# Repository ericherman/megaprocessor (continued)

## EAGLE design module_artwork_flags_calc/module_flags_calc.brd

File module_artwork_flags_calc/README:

Flag Calculation

The status flags are calculated using the results generated by various
parts of the processor, in particular the ALU, depending on the
instruction being executed. They are stored in the status register.

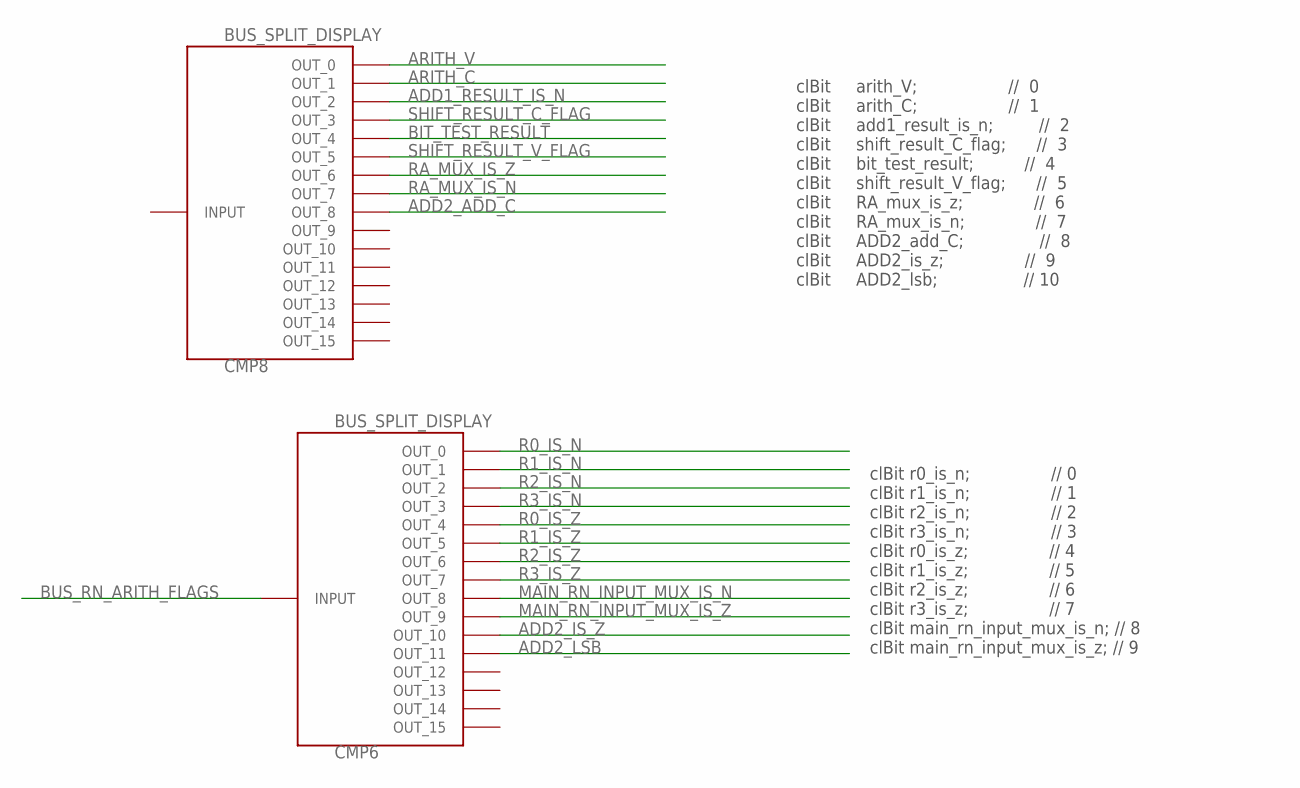
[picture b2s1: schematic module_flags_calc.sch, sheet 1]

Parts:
CMP6, CMP8: BUS_SPLIT_DISPLAY

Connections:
ADD1_RESULT_IS_N: CMP8.P$3 (OUT_2); also elsewhere on the board
ADD2_ADD_C: CMP8.P$9 (OUT_8); also elsewhere on the board
ADD2_IS_Z: CMP6.P$11 (OUT_10); also elsewhere on the board
ADD2_LSB: CMP6.P$12 (OUT_11); also elsewhere on the board
ARITH_C: CMP8.P$2 (OUT_1); also elsewhere on the board
ARITH_V: CMP8.P$1 (OUT_0); also elsewhere on the board
BIT_TEST_RESULT: CMP8.P$5 (OUT_4); also elsewhere on the board
BUS_RN_ARITH_FLAGS: CMP6.INPUT
MAIN_RN_INPUT_MUX_IS_N: CMP6.P$9 (OUT_8); also elsewhere on the board
MAIN_RN_INPUT_MUX_IS_Z: CMP6.P$10 (OUT_9); also elsewhere on the board
R0_IS_N: CMP6.P$1 (OUT_0); also elsewhere on the board
R0_IS_Z: CMP6.P$5 (OUT_4)
R1_IS_N: CMP6.P$2 (OUT_1); also elsewhere on the board
R1_IS_Z: CMP6.P$6 (OUT_5)
R2_IS_N: CMP6.P$3 (OUT_2)
R2_IS_Z: CMP6.P$7 (OUT_6)
R3_IS_N: CMP6.P$4 (OUT_3)
R3_IS_Z: CMP6.P$8 (OUT_7)
RA_MUX_IS_N: CMP8.P$8 (OUT_7); also elsewhere on the board
RA_MUX_IS_Z: CMP8.P$7 (OUT_6); also elsewhere on the board
SHIFT_RESULT_C_FLAG: CMP8.P$4 (OUT_3); also elsewhere on the board
SHIFT_RESULT_V_FLAG: CMP8.P$6 (OUT_5); also elsewhere on the board

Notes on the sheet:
clBit arith_V; // 0 clBit arith_C; // 1 clBit add1_result_is_n; // 2 clBit shift_result_C_flag; // 3 clBit bit_test_result; // 4 clBit shift_result_V_flag; // 5 clBit RA_mux_is_z; // 6 clBit RA_mux_is_n; // 7 clBit ADD2_add_C; // 8 clBit ADD2_is_z; // 9 clBit ADD2_lsb; // 10
clBit r0_is_n; // 0 clBit r1_is_n; // 1 clBit r2_is_n; // 2 clBit r3_is_n; // 3 clBit r0_is_z; // 4 clBit r1_is_z; // 5 clBit r2_is_z; // 6 clBit r3_is_z; // 7 clBit main_rn_input_mux_is_n; // 8 clBit main_rn_input_mux_is_z; // 9

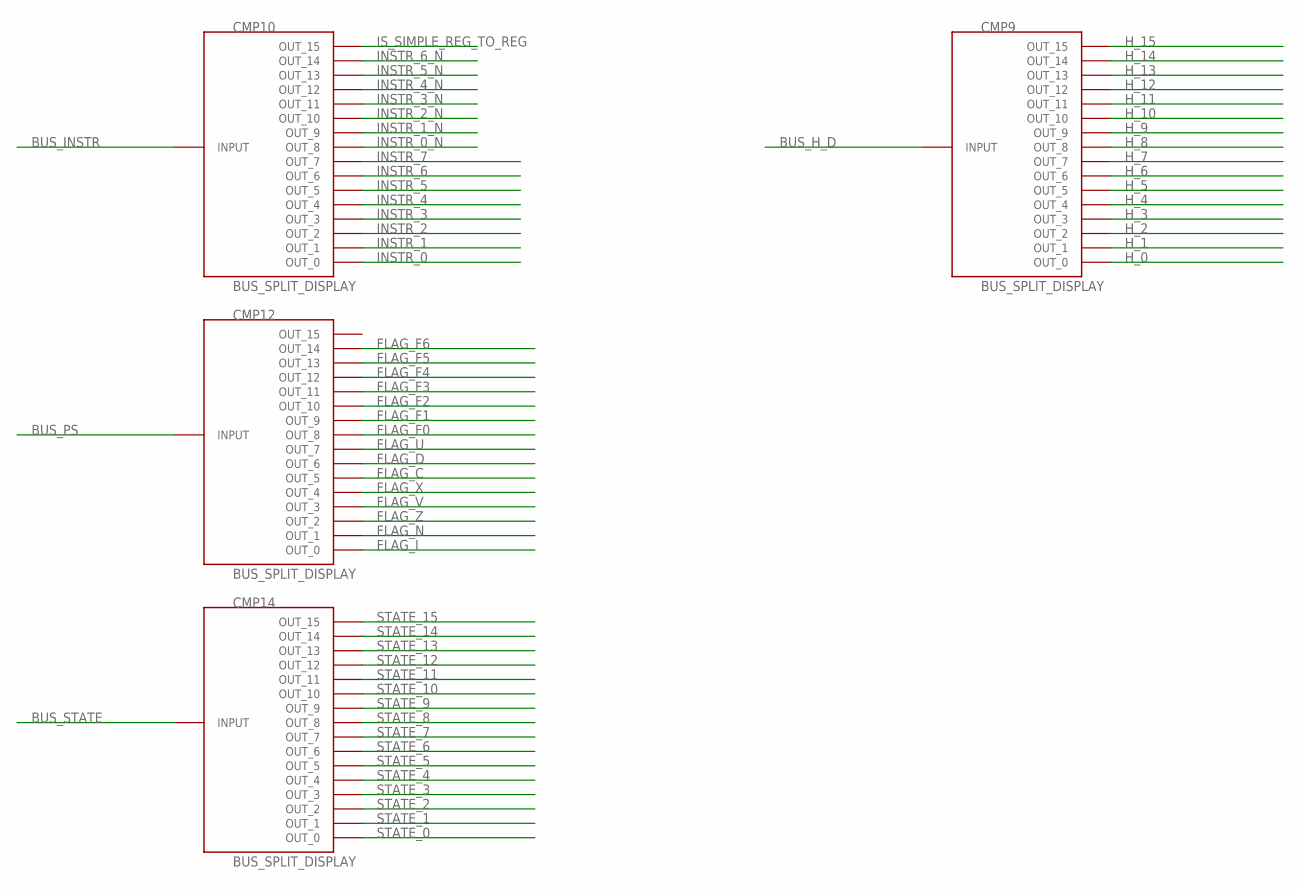
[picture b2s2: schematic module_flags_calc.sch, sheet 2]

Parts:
CMP9, CMP10, CMP12, CMP14: BUS_SPLIT_DISPLAY

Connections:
BUS_H_D: CMP9.INPUT
BUS_INSTR: CMP10.INPUT
BUS_PS: CMP12.INPUT
BUS_STATE: CMP14.INPUT
FLAG_C: CMP12.P$6 (OUT_5); also elsewhere on the board
FLAG_D: CMP12.P$7 (OUT_6); also elsewhere on the board
FLAG_F0: CMP12.P$9 (OUT_8); also elsewhere on the board
FLAG_F1: CMP12.P$10 (OUT_9); also elsewhere on the board
FLAG_F2: CMP12.P$11 (OUT_10)
FLAG_F3: CMP12.P$12 (OUT_11)
FLAG_F4: CMP12.P$13 (OUT_12); also elsewhere on the board
FLAG_F5: CMP12.P$14 (OUT_13); also elsewhere on the board
FLAG_F6: CMP12.P$15 (OUT_14); also elsewhere on the board
FLAG_I: CMP12.P$1 (OUT_0); also elsewhere on the board
FLAG_N: CMP12.P$2 (OUT_1); also elsewhere on the board
FLAG_U: CMP12.P$8 (OUT_7); also elsewhere on the board
FLAG_V: CMP12.P$4 (OUT_3); also elsewhere on the board
FLAG_X: CMP12.P$5 (OUT_4); also elsewhere on the board
FLAG_Z: CMP12.P$3 (OUT_2); also elsewhere on the board
H_0: CMP9.P$1 (OUT_0)
H_1: CMP9.P$2 (OUT_1)
H_2: CMP9.P$3 (OUT_2)
H_3: CMP9.P$4 (OUT_3); also elsewhere on the board
H_4: CMP9.P$5 (OUT_4); also elsewhere on the board
H_5: CMP9.P$6 (OUT_5); also elsewhere on the board
H_6: CMP9.P$7 (OUT_6)
H_7: CMP9.P$8 (OUT_7)
H_8: CMP9.P$9 (OUT_8)
H_9: CMP9.P$10 (OUT_9)
H_10: CMP9.P$11 (OUT_10)
H_11: CMP9.P$12 (OUT_11)
H_12: CMP9.P$13 (OUT_12)
H_13: CMP9.P$14 (OUT_13)
H_14: CMP9.P$15 (OUT_14)
H_15: CMP9.P$16 (OUT_15)
INSTR_0: CMP10.P$1 (OUT_0); also elsewhere on the board
INSTR_0_N: CMP10.P$9 (OUT_8)
INSTR_1: CMP10.P$2 (OUT_1); also elsewhere on the board
INSTR_1_N: CMP10.P$10 (OUT_9)
INSTR_2: CMP10.P$3 (OUT_2); also elsewhere on the board
INSTR_2_N: CMP10.P$11 (OUT_10)
INSTR_3: CMP10.P$4 (OUT_3); also elsewhere on the board
INSTR_3_N: CMP10.P$12 (OUT_11)
INSTR_4: CMP10.P$5 (OUT_4)
INSTR_4_N: CMP10.P$13 (OUT_12)
INSTR_5: CMP10.P$6 (OUT_5)
INSTR_5_N: CMP10.P$14 (OUT_13)
INSTR_6: CMP10.P$7 (OUT_6)
INSTR_6_N: CMP10.P$15 (OUT_14); also elsewhere on the board
INSTR_7: CMP10.P$8 (OUT_7)
IS_SIMPLE_REG_TO_REG: CMP10.P$16 (OUT_15); also elsewhere on the board
STATE_0: CMP14.P$1 (OUT_0); also elsewhere on the board
STATE_1: CMP14.P$2 (OUT_1); also elsewhere on the board
STATE_2: CMP14.P$3 (OUT_2)
STATE_3: CMP14.P$4 (OUT_3); also elsewhere on the board
STATE_4: CMP14.P$5 (OUT_4)
STATE_5: CMP14.P$6 (OUT_5); also elsewhere on the board
STATE_6: CMP14.P$7 (OUT_6)
STATE_7: CMP14.P$8 (OUT_7)
STATE_8: CMP14.P$9 (OUT_8); also elsewhere on the board
STATE_9: CMP14.P$10 (OUT_9); also elsewhere on the board
STATE_10: CMP14.P$11 (OUT_10)
STATE_11: CMP14.P$12 (OUT_11)
STATE_12: CMP14.P$13 (OUT_12)
STATE_13: CMP14.P$14 (OUT_13); also elsewhere on the board
STATE_14: CMP14.P$15 (OUT_14)
STATE_15: CMP14.P$16 (OUT_15)

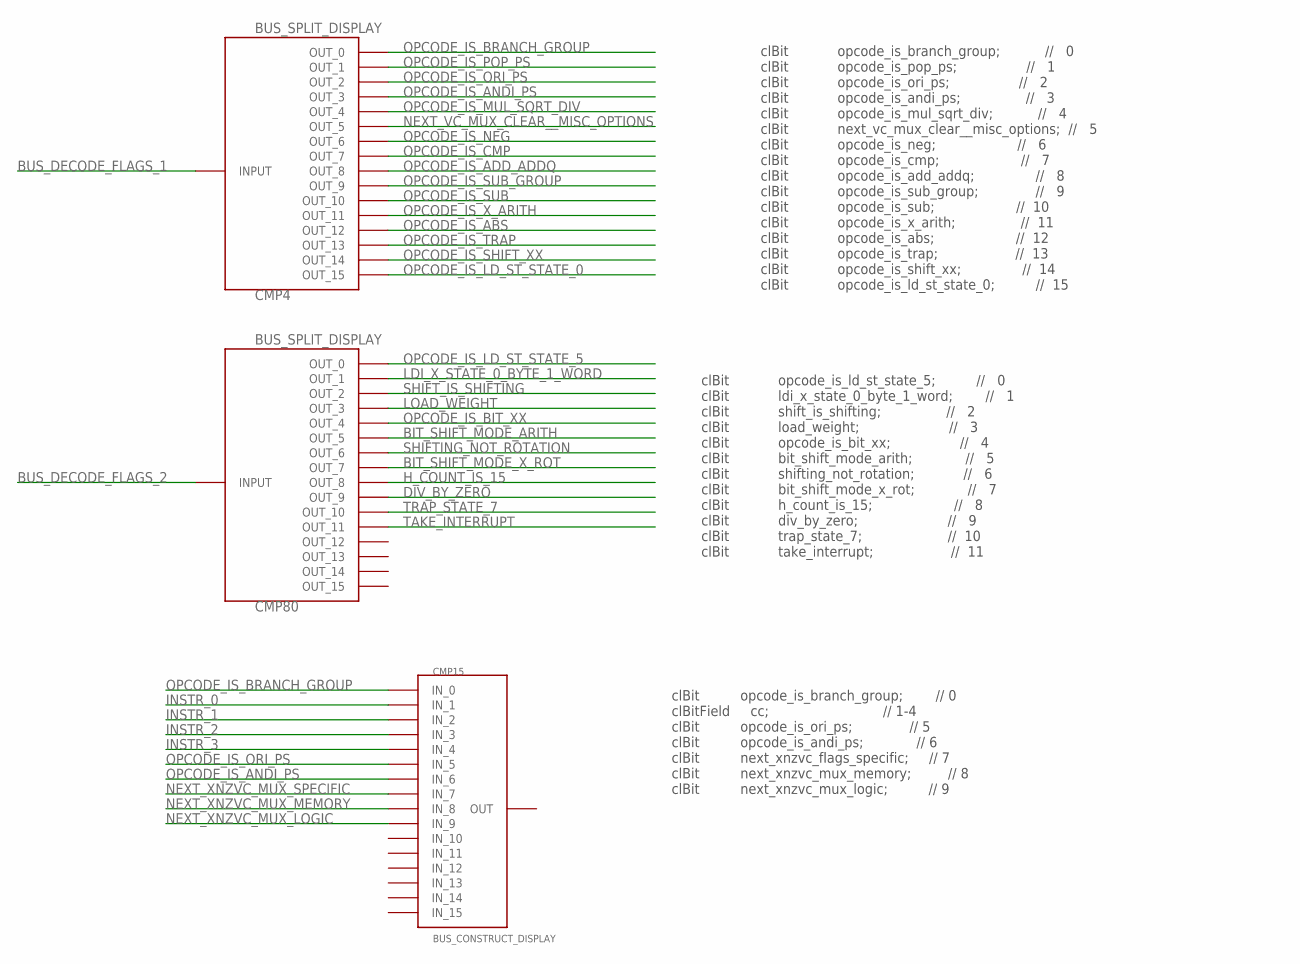
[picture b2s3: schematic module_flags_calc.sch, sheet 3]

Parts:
CMP4, CMP80: BUS_SPLIT_DISPLAY
CMP15: BUS_CONSTRUCT_DISPLAY; BUS_SPLIT_DISPLAY

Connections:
BIT_SHIFT_MODE_ARITH: CMP80.P$6 (OUT_5); also elsewhere on the board
BIT_SHIFT_MODE_X_ROT: CMP80.P$8 (OUT_7); also elsewhere on the board
BUS_DECODE_FLAGS_1: CMP4.INPUT
BUS_DECODE_FLAGS_2: CMP80.INPUT
DIV_BY_ZERO: CMP80.P$10 (OUT_9); also elsewhere on the board
H_COUNT_IS_15: CMP80.P$9 (OUT_8); also elsewhere on the board
INSTR_0: CMP15.P$2 (IN_1); also elsewhere on the board
INSTR_1: CMP15.P$3 (IN_2); also elsewhere on the board
INSTR_2: CMP15.P$4 (IN_3); also elsewhere on the board
INSTR_3: CMP15.P$5 (IN_4); also elsewhere on the board
LDI_X_STATE_0_BYTE_1_WORD: CMP80.P$2 (OUT_1); also elsewhere on the board
LOAD_WEIGHT: CMP80.P$4 (OUT_3); also elsewhere on the board
NEXT_VC_MUX_CLEAR__MISC_OPTIONS: CMP4.P$6 (OUT_5); also elsewhere on the board
NEXT_XNZVC_MUX_LOGIC: CMP15.P$10 (IN_9); also elsewhere on the board
NEXT_XNZVC_MUX_MEMORY: CMP15.P$9 (IN_8); also elsewhere on the board
NEXT_XNZVC_MUX_SPECIFIC: CMP15.P$8 (IN_7); also elsewhere on the board
OPCODE_IS_ABS: CMP4.P$13 (OUT_12); also elsewhere on the board
OPCODE_IS_ADD_ADDQ: CMP4.P$9 (OUT_8); also elsewhere on the board
OPCODE_IS_ANDI_PS: CMP4.P$4 (OUT_3), CMP15.P$7 (IN_6); also elsewhere on the board
OPCODE_IS_BIT_XX: CMP80.P$5 (OUT_4); also elsewhere on the board
OPCODE_IS_BRANCH_GROUP: CMP4.P$1 (OUT_0), CMP15.P$1 (IN_0)
OPCODE_IS_CMP: CMP4.P$8 (OUT_7); also elsewhere on the board
OPCODE_IS_LD_ST_STATE_0: CMP4.P$16 (OUT_15); also elsewhere on the board
OPCODE_IS_LD_ST_STATE_5: CMP80.P$1 (OUT_0); also elsewhere on the board
OPCODE_IS_MUL_SQRT_DIV: CMP4.P$5 (OUT_4); also elsewhere on the board
OPCODE_IS_NEG: CMP4.P$7 (OUT_6); also elsewhere on the board
OPCODE_IS_ORI_PS: CMP4.P$3 (OUT_2), CMP15.P$6 (IN_5); also elsewhere on the board
OPCODE_IS_POP_PS: CMP4.P$2 (OUT_1); also elsewhere on the board
OPCODE_IS_SHIFT_XX: CMP4.P$15 (OUT_14); also elsewhere on the board
OPCODE_IS_SUB: CMP4.P$11 (OUT_10); also elsewhere on the board
OPCODE_IS_SUB_GROUP: CMP4.P$10 (OUT_9); also elsewhere on the board
OPCODE_IS_TRAP: CMP4.P$14 (OUT_13); also elsewhere on the board
OPCODE_IS_X_ARITH: CMP4.P$12 (OUT_11); also elsewhere on the board
SHIFTING_NOT_ROTATION: CMP80.P$7 (OUT_6); also elsewhere on the board
SHIFT_IS_SHIFTING: CMP80.P$3 (OUT_2); also elsewhere on the board
TAKE_INTERRUPT: CMP80.P$12 (OUT_11); also elsewhere on the board
TRAP_STATE_7: CMP80.P$11 (OUT_10); also elsewhere on the board

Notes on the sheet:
clBit opcode_is_branch_group; // 0 clBit opcode_is_pop_ps; // 1 clBit opcode_is_ori_ps; // 2 clBit opcode_is_andi_ps; // 3 clBit opcode_is_mul_sqrt_div; // 4 clBit next_vc_mux_clear__misc_options; // 5 clBit opcode_is_neg; // 6 clBit opcode_is_cmp; // 7 clBit opcode_is_add_addq; // 8 clBit opcode_i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
clBit opcode_is_ld_st_state_5; // 0 clBit ldi_x_state_0_byte_1_word; // 1 clBit shift_is_shifting; // 2 clBit load_weight; // 3 clBit opcode_is_bit_xx; // 4 clBit bit_shift_mode_arith; // 5 clBit shifting_not_rotation; // 6 clBit bit_shift_mode_x_rot; // 7 clBit h_count_is_15; // 8 clBit div_by_zer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
clBit opcode_is_branch_group; // 0 clBitField cc; // 1-4 clBit opcode_is_ori_ps; // 5 clBit opcode_is_andi_ps; // 6 clBit next_xnzvc_flags_specific; // 7 clBit next_xnzvc_mux_memory; // 8 clBit next_xnzvc_mux_logic; // 9

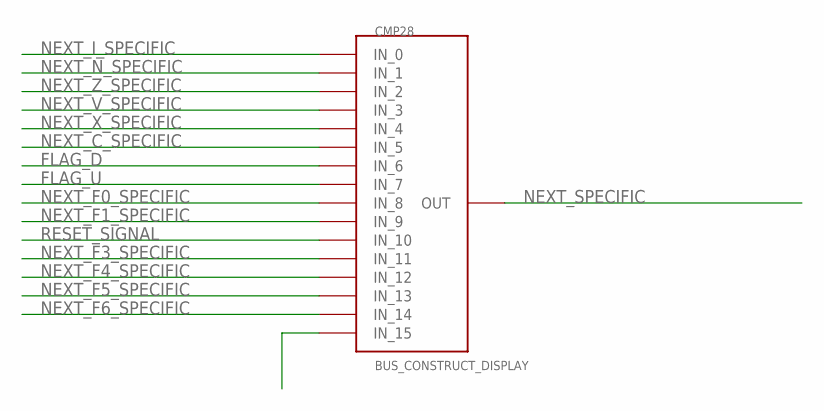
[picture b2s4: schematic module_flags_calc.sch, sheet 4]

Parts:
CMP28: BUS_CONSTRUCT_DISPLAY; BUS_SPLIT_DISPLAY

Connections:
FLAG_D: CMP28.P$7 (IN_6); also elsewhere on the board
FLAG_U: CMP28.P$8 (IN_7); also elsewhere on the board
NEXT_C_SPECIFIC: CMP28.P$6 (IN_5); also elsewhere on the board
NEXT_F0_SPECIFIC: CMP28.P$9 (IN_8); also elsewhere on the board
NEXT_F1_SPECIFIC: CMP28.P$10 (IN_9); also elsewhere on the board
NEXT_F3_SPECIFIC: CMP28.P$12 (IN_11); also elsewhere on the board
NEXT_F4_SPECIFIC: CMP28.P$13 (IN_12); also elsewhere on the board
NEXT_F5_SPECIFIC: CMP28.P$14 (IN_13); also elsewhere on the board
NEXT_F6_SPECIFIC: CMP28.P$15 (IN_14); also elsewhere on the board
NEXT_I_SPECIFIC: CMP28.P$1 (IN_0); also elsewhere on the board
NEXT_N_SPECIFIC: CMP28.P$2 (IN_1); also elsewhere on the board
NEXT_SPECIFIC: CMP28.INPUT (OUT)
NEXT_V_SPECIFIC: CMP28.P$4 (IN_3); also elsewhere on the board
NEXT_X_SPECIFIC: CMP28.P$5 (IN_4); also elsewhere on the board
NEXT_Z_SPECIFIC: CMP28.P$3 (IN_2); also elsewhere on the board
RESET_SIGNAL: CMP28.P$11 (IN_10)

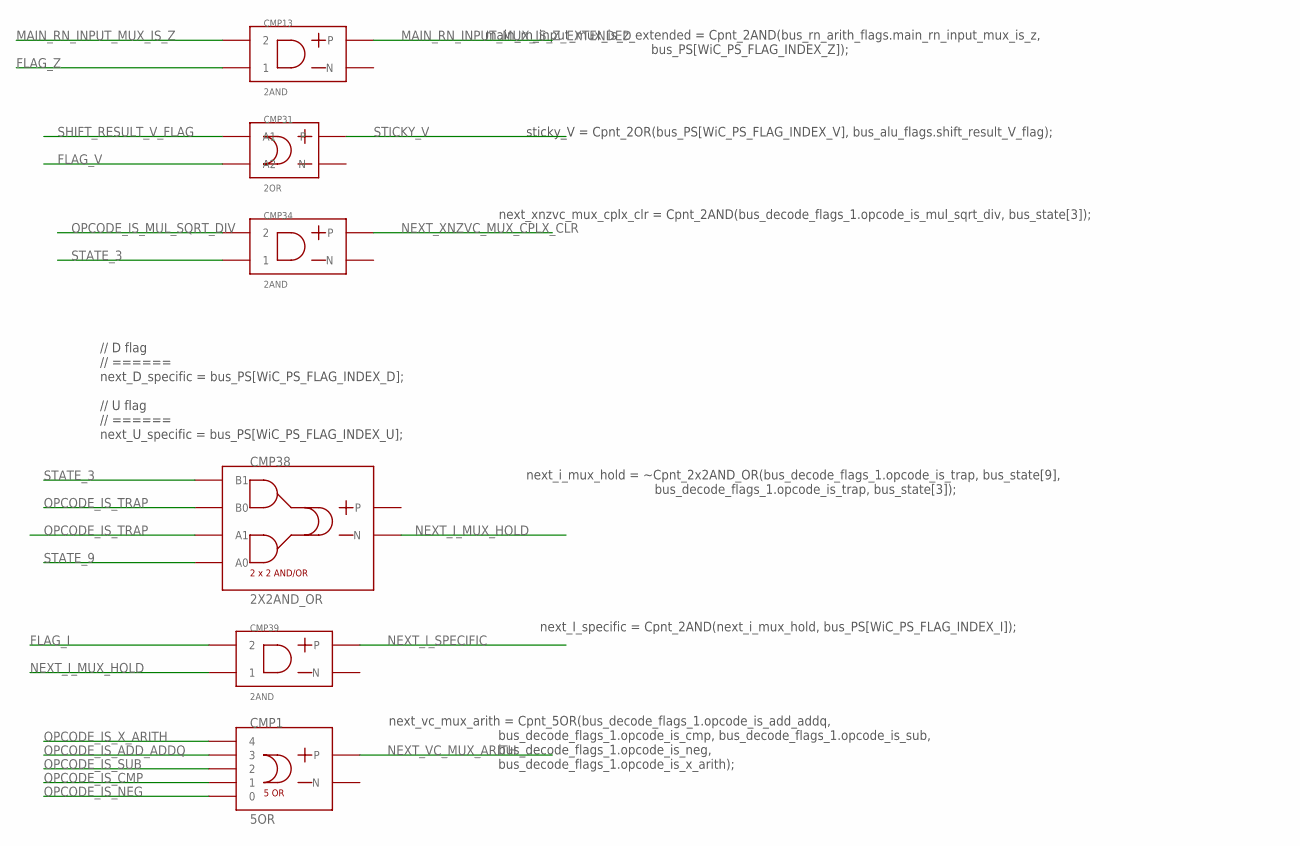
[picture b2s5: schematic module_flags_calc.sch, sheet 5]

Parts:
CMP1: 5OR
CMP13, CMP34, CMP39: 2AND
CMP31: 2OR
CMP38: 2X2AND_OR

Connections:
FLAG_I: CMP39.P$2 (2); also elsewhere on the board
FLAG_V: CMP31.P$1 (A2); also elsewhere on the board
FLAG_Z: CMP13.P$1 (1); also elsewhere on the board
MAIN_RN_INPUT_MUX_IS_Z: CMP13.P$2 (2); also elsewhere on the board
MAIN_RN_INPUT_MUX_IS_Z_EXTENDED: CMP13.OUT_P; also elsewhere on the board
NEXT_I_MUX_HOLD: CMP38.OUT_M (N), CMP39.P$1 (1)
NEXT_I_SPECIFIC: CMP39.OUT_P; also elsewhere on the board
NEXT_VC_MUX_ARITH: CMP1.OUT_P; also elsewhere on the board
NEXT_XNZVC_MUX_CPLX_CLR: CMP34.OUT_P; also elsewhere on the board
OPCODE_IS_ADD_ADDQ: CMP1.4 (3); also elsewhere on the board
OPCODE_IS_CMP: CMP1.2 (1); also elsewhere on the board
OPCODE_IS_MUL_SQRT_DIV: CMP34.P$2 (2); also elsewhere on the board
OPCODE_IS_NEG: CMP1.1 (0); also elsewhere on the board
OPCODE_IS_SUB: CMP1.3 (2); also elsewhere on the board
OPCODE_IS_TRAP: CMP38.P$2 (A1), CMP38.P$3 (B0); also elsewhere on the board
OPCODE_IS_X_ARITH: CMP1.5 (4); also elsewhere on the board
SHIFT_RESULT_V_FLAG: CMP31.P$2 (A1); also elsewhere on the board
STATE_3: CMP34.P$1 (1), CMP38.P$4 (B1); also elsewhere on the board
STATE_9: CMP38.P$1 (A0); also elsewhere on the board
STICKY_V: CMP31.OUT_P; also elsewhere on the board

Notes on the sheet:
sticky_V = Cpnt_2OR(bus_PS[WiC_PS_FLAG_INDEX_V], bus_alu_flags.shift_result_V_flag);
next_xnzvc_mux_cplx_clr = Cpnt_2AND(bus_decode_flags_1.opcode_is_mul_sqrt_div, bus_state[3]);
// D flag // ====== next_D_specific = bus_PS[WiC_PS_FLAG_INDEX_D]; // U flag // ====== next_U_specific = bus_PS[WiC_PS_FLAG_INDEX_U];
next_i_mux_hold = ~Cpnt_2x2AND_OR(bus_decode_flags_1.opcode_is_trap, bus_state[9], bus_decode_flags_1.opcode_is_trap, bus_state[3]);
next_I_specific = Cpnt_2AND(next_i_mux_hold, bus_PS[WiC_PS_FLAG_INDEX_I]);
next_vc_mux_arith = Cpnt_5OR(bus_decode_flags_1.opcode_is_add_addq, bus_decode_flags_1.opcode_is_cmp, bus_decode_flags_1.opcode_is_sub, bus_decode_flags_1.opcode_is_neg, bus_decode_flags_1.opcode_is_x_arith);
main_rn_input_mux_is_z_extended = Cpnt_2AND(bus_rn_arith_flags.main_rn_input_mux_is_z, bus_PS[WiC_PS_FLAG_INDEX_Z]);

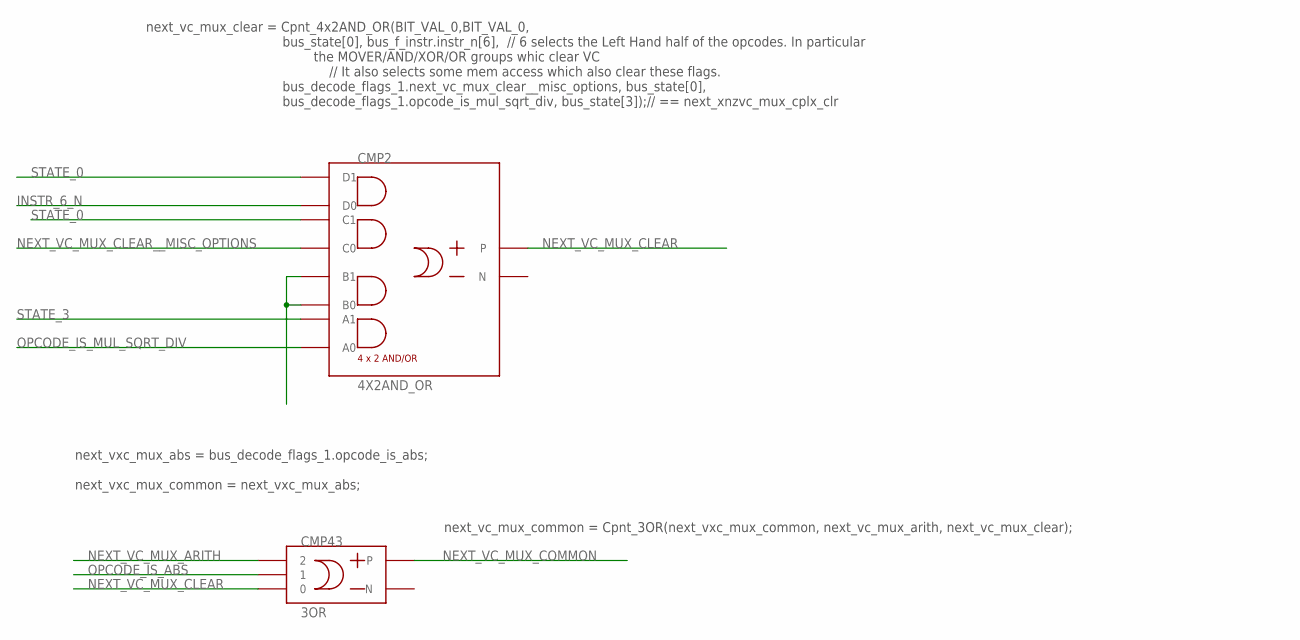
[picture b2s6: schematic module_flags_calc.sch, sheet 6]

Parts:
CMP2: 4X2AND_OR
CMP43: 3OR

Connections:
INSTR_6_N: CMP2.P$7 (D0); also elsewhere on the board
unnamed: CMP2.P$3 (B0), CMP2.P$4 (B1)
NEXT_VC_MUX_ARITH: CMP43.P$3 (2); also elsewhere on the board
NEXT_VC_MUX_CLEAR: CMP2.OUT_P, CMP43.P$1 (0)
NEXT_VC_MUX_CLEAR__MISC_OPTIONS: CMP2.P$5 (C0); also elsewhere on the board
NEXT_VC_MUX_COMMON: CMP43.OUT_P; also elsewhere on the board
OPCODE_IS_ABS: CMP43.P$2 (1); also elsewhere on the board
OPCODE_IS_MUL_SQRT_DIV: CMP2.P$1 (A0); also elsewhere on the board
STATE_0: CMP2.P$6 (C1), CMP2.P$8 (D1); also elsewhere on the board
STATE_3: CMP2.P$2 (A1); also elsewhere on the board

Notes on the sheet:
next_vc_mux_clear = Cpnt_4x2AND_OR(BIT_VAL_0,BIT_VAL_0, bus_state[0], bus_f_instr.instr_n[6], // 6 selects the Left Hand half of the opcodes. In particular the MOVER/AND/XOR/OR groups whic clear VC // It also selects some mem access which also clear these flags. bus_decode_flags_1.next_vc_mux_clear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
next_vxc_mux_abs = bus_decode_flags_1.opcode_is_abs; next_vxc_mux_common = next_vxc_mux_abs;
next_vc_mux_common = Cpnt_3OR(next_vxc_mux_common, next_vc_mux_arith, next_vc_mux_clear);

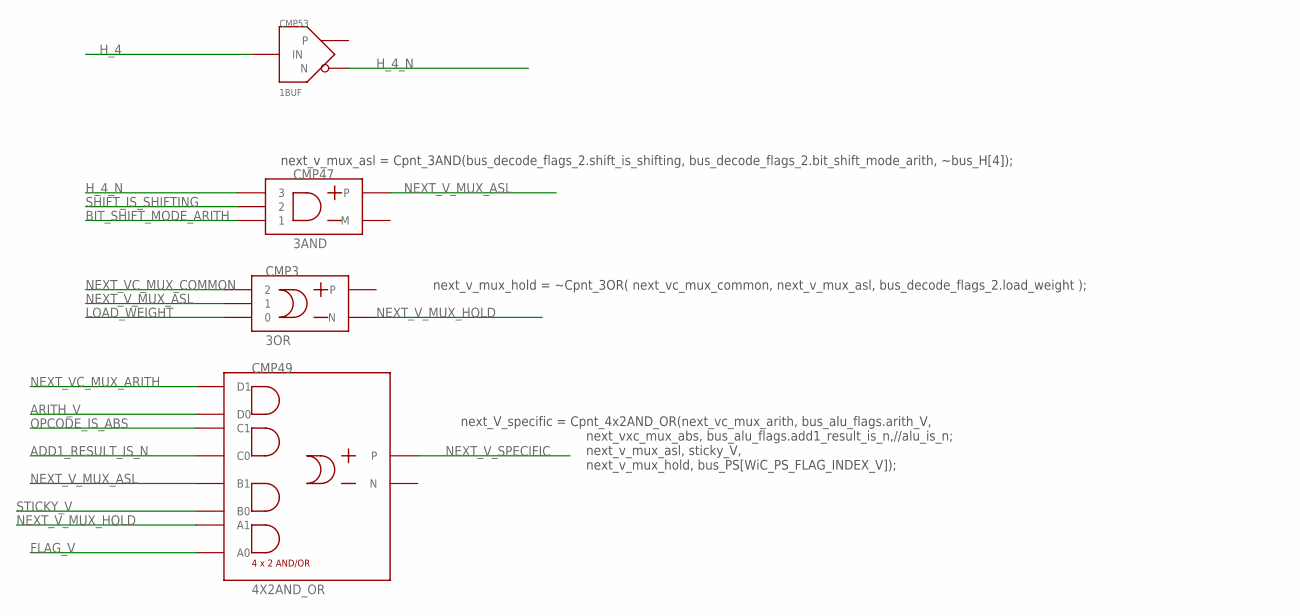
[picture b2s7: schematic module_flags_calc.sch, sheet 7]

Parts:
CMP3: 3OR
CMP47: 3AND
CMP49: 4X2AND_OR
CMP53: 1BUF

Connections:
ADD1_RESULT_IS_N: CMP49.P$5 (C0); also elsewhere on the board
ARITH_V: CMP49.P$7 (D0); also elsewhere on the board
BIT_SHIFT_MODE_ARITH: CMP47.P$1 (1); also elsewhere on the board
FLAG_V: CMP49.P$1 (A0); also elsewhere on the board
H_4: CMP53.IN; also elsewhere on the board
H_4_N: CMP47.P$3 (3), CMP53.N
LOAD_WEIGHT: CMP3.P$1 (0); also elsewhere on the board
NEXT_VC_MUX_ARITH: CMP49.P$8 (D1); also elsewhere on the board
NEXT_VC_MUX_COMMON: CMP3.P$3 (2); also elsewhere on the board
NEXT_V_MUX_ASL: CMP3.P$2 (1), CMP47.OUT_P, CMP49.P$4 (B1)
NEXT_V_MUX_HOLD: CMP3.OUT_M (N), CMP49.P$2 (A1)
NEXT_V_SPECIFIC: CMP49.OUT_P; also elsewhere on the board
OPCODE_IS_ABS: CMP49.P$6 (C1); also elsewhere on the board
SHIFT_IS_SHIFTING: CMP47.P$2 (2); also elsewhere on the board
STICKY_V: CMP49.P$3 (B0); also elsewhere on the board

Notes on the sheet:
next_v_mux_asl = Cpnt_3AND(bus_decode_flags_2.shift_is_shifting, bus_decode_flags_2.bit_shift_mode_arith, ~bus_H[4]);
next_v_mux_hold = ~Cpnt_3OR( next_vc_mux_common, next_v_mux_asl, bus_decode_flags_2.load_weight );
next_V_specific = Cpnt_4x2AND_OR(next_vc_mux_arith, bus_alu_flags.arith_V, next_vxc_mux_abs, bus_alu_flags.add1_result_is_n,//alu_is_n; next_v_mux_asl, sticky_V, next_v_mux_hold, bus_PS[WiC_PS_FLAG_INDEX_V]);

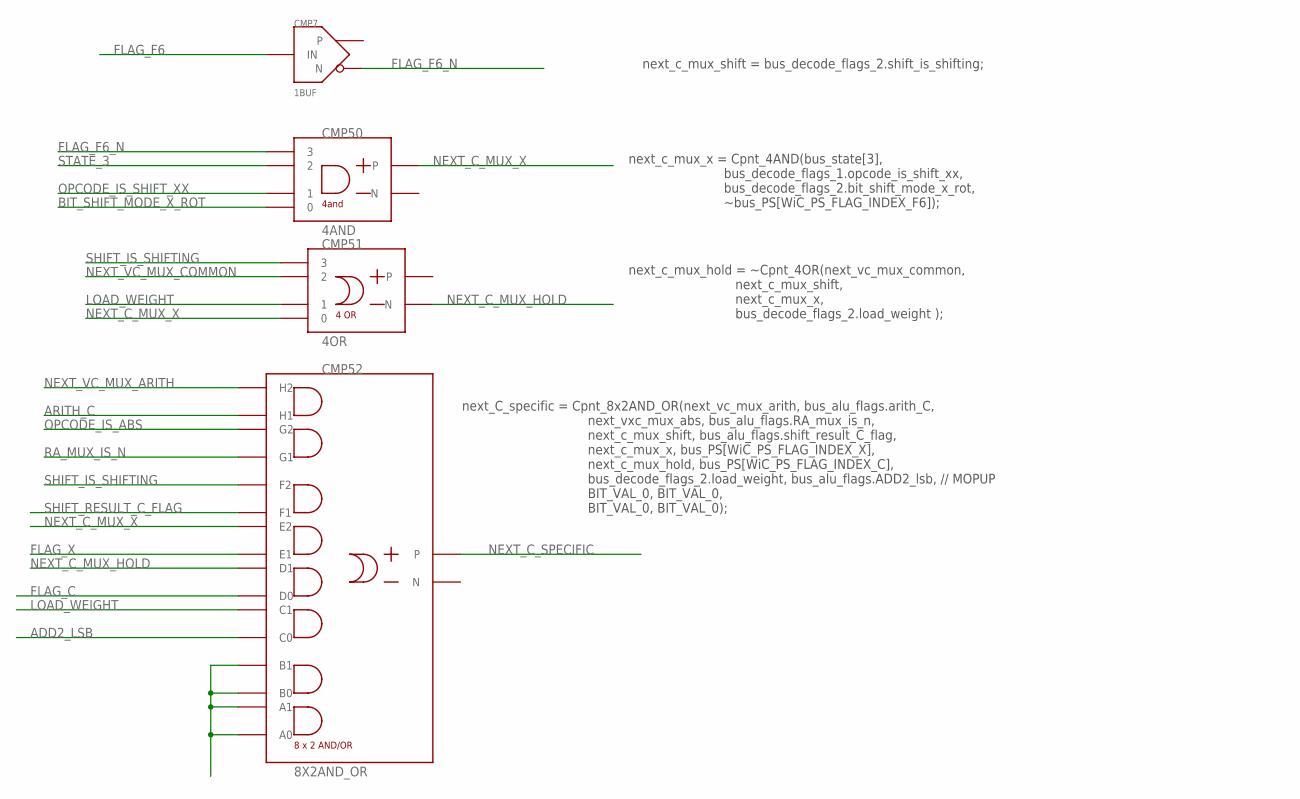
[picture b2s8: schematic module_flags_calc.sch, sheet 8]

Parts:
CMP7: 1BUF
CMP50: 4AND
CMP51: 4OR
CMP52: 8X2AND_OR

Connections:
ADD2_LSB: CMP52.P$5 (C0); also elsewhere on the board
ARITH_C: CMP52.P$15 (H1); also elsewhere on the board
BIT_SHIFT_MODE_X_ROT: CMP50.P$1 (0); also elsewhere on the board
FLAG_C: CMP52.P$7 (D0); also elsewhere on the board
FLAG_F6: CMP7.IN; also elsewhere on the board
FLAG_F6_N: CMP7.N, CMP50.P$4 (3)
FLAG_X: CMP52.P$9 (E1); also elsewhere on the board
LOAD_WEIGHT: CMP51.2 (1), CMP52.P$6 (C1); also elsewhere on the board
unnamed: CMP52.P$1 (A0), CMP52.P$2 (A1), CMP52.P$3 (B0), CMP52.P$4 (B1)
NEXT_C_MUX_HOLD: CMP51.OUT_M (N), CMP52.P$8 (D1)
NEXT_C_MUX_X: CMP50.OUT_P, CMP51.1 (0), CMP52.P$10 (E2)
NEXT_C_SPECIFIC: CMP52.OUT_P; also elsewhere on the board
NEXT_VC_MUX_ARITH: CMP52.P$16 (H2); also elsewhere on the board
NEXT_VC_MUX_COMMON: CMP51.3 (2); also elsewhere on the board
OPCODE_IS_ABS: CMP52.P$14 (G2); also elsewhere on the board
OPCODE_IS_SHIFT_XX: CMP50.P$2 (1); also elsewhere on the board
RA_MUX_IS_N: CMP52.P$13 (G1); also elsewhere on the board
SHIFT_IS_SHIFTING: CMP51.4 (3), CMP52.P$12 (F2); also elsewhere on the board
SHIFT_RESULT_C_FLAG: CMP52.P$11 (F1); also elsewhere on the board
STATE_3: CMP50.P$3 (2); also elsewhere on the board

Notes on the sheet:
next_c_mux_shift = bus_decode_flags_2.shift_is_shifting;
next_c_mux_x = Cpnt_4AND(bus_state[3], bus_decode_flags_1.opcode_is_shift_xx, bus_decode_flags_2.bit_shift_mode_x_rot, ~bus_PS[WiC_PS_FLAG_INDEX_F6]);
next_c_mux_hold = ~Cpnt_4OR(next_vc_mux_common, next_c_mux_shift, next_c_mux_x, bus_decode_flags_2.load_weight );
next_C_specific = Cpnt_8x2AND_OR(next_vc_mux_arith, bus_alu_flags.arith_C, next_vxc_mux_abs, bus_alu_flags.RA_mux_is_n, next_c_mux_shift, bus_alu_flags.shift_result_C_flag, next_c_mux_x, bus_PS[WiC_PS_FLAG_INDEX_X], next_c_mux_hold, bus_PS[WiC_PS_FLAG_INDEX_C], bus_decode_flags_2.load_weight, bus_a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

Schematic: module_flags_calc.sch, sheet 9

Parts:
CMP5: 4OR
CMP56: 5OR
CMP57: 4X2AND_OR

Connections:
ADD2_ADD_C: CMP57.P$1 (A0); also elsewhere on the board
FLAG_X: CMP57.P$3 (B0); also elsewhere on the board
LOAD_WEIGHT: CMP56.3 (2); also elsewhere on the board
NEXT_C_SPECIFIC: CMP57.P$5 (C0); also elsewhere on the board
NEXT_XNZVC_MUX_CPLX_CLR: CMP56.1 (0); also elsewhere on the board
NEXT_X_MUX_HOLD: CMP56.OUT_M (N), CMP57.P$4 (B1)
NEXT_X_MUX_UPDATE: CMP5.OUT_P, CMP56.4 (3), CMP57.P$6 (C1)
NEXT_X_SPECIFIC: CMP57.OUT_P; also elsewhere on the board
OPCODE_IS_ABS: CMP56.5 (4), CMP57.P$8 (D1); also elsewhere on the board
OPCODE_IS_ADD_ADDQ: CMP5.2 (1); also elsewhere on the board
OPCODE_IS_SUB_GROUP: CMP5.4 (3); also elsewhere on the board
OPCODE_IS_X_ARITH: CMP5.1 (0); also elsewhere on the board
RA_MUX_IS_N: CMP57.P$7 (D0); also elsewhere on the board
SHIFTING_NOT_ROTATION: CMP5.3 (2); also elsewhere on the board
STATE_13: CMP56.2 (1), CMP57.P$2 (A1); also elsewhere on the board

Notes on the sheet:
next_x_mux_update = Cpnt_4OR(bus_decode_flags_1.opcode_is_add_addq, bus_decode_flags_1.opcode_is_sub_group, bus_decode_flags_1.opcode_is_x_arith, bus_decode_flags_2.shifting_not_rotation);//next_x_mux_update__shifting);
next_x_mux_mul = bus_state[13];
next_x_mux_hold = ~Cpnt_5OR(next_vxc_mux_common, next_x_mux_update, next_x_mux_mul, next_xnzvc_mux_cplx_clr, bus_decode_flags_2.load_weight);
next_X_specific = Cpnt_4x2AND_OR(next_vxc_mux_abs, bus_alu_flags.RA_mux_is_n, next_x_mux_update,next_C_specific, // <<----<<<< MUST be AFTER C logic next_x_mux_hold, bus_PS[WiC_PS_FLAG_INDEX_X], next_x_mux_mul,bus_alu_flags.ADD2_add_C);

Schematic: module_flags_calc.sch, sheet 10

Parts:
CMP11, CMP59: 4OR
CMP61: 2X2AND_OR
CMP63: 2OR
CMP64: 4X2AND_OR

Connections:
FLAG_N: CMP64.P$1 (A0); also elsewhere on the board
INSTR_3: CMP61.P$4 (B1); also elsewhere on the board
IS_SIMPLE_REG_TO_REG: CMP59.4 (3); also elsewhere on the board
LDI_X_STATE_0_BYTE_1_WORD: CMP59.2 (1); also elsewhere on the board
LOAD_WEIGHT: CMP11.4 (3); also elsewhere on the board
MAIN_RN_INPUT_MUX_IS_N: CMP64.P$5 (C0), CMP64.P$7 (D0); also elsewhere on the board
NEXT_NZ_MUX_COMMON: CMP11.OUT_P, CMP63.P$2 (A1); also elsewhere on the board
NEXT_NZ_MUX_MAIN: CMP11.2 (1), CMP59.OUT_P, CMP64.P$8 (D1); also elsewhere on the board
NEXT_NZ_MUX_RAC: CMP11.1 (0), CMP61.OUT_P, CMP64.P$4 (B1); also elsewhere on the board
NEXT_N_MUX_HOLD: CMP63.OUT_M (N), CMP64.P$2 (A1)
NEXT_N_SPECIFIC: CMP64.OUT_P; also elsewhere on the board
NEXT_XNZVC_MUX_CPLX_CLR: CMP63.P$1 (A2); also elsewhere on the board
OPCODE_IS_LD_ST_STATE_0: CMP61.P$3 (B0); also elsewhere on the board
OPCODE_IS_LD_ST_STATE_5: CMP59.1 (0); also elsewhere on the board
OPCODE_IS_SHIFT_XX: CMP61.P$1 (A0); also elsewhere on the board
OPCODE_IS_X_ARITH: CMP11.3 (2), CMP64.P$6 (C1); also elsewhere on the board
RA_MUX_IS_N: CMP64.P$3 (B0); also elsewhere on the board
SHIFT_IS_SHIFTING: CMP59.3 (2); also elsewhere on the board
STATE_0: CMP61.P$2 (A1); also elsewhere on the board

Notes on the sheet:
next_nz_mux_main = Cpnt_4OR( is_simple_reg_to_reg, bus_decode_flags_2.shift_is_shifting, bus_decode_flags_2.ldi_x_state_0_byte_1_word, bus_decode_flags_2.opcode_is_ld_st_state_5);//next_nz_mux_main_mem);
next_nz_mux_main_extended = bus_decode_flags_1.opcode_is_x_arith;
next_nz_mux_RAC = Cpnt_2x2AND_OR(bus_decode_flags_1.opcode_is_ld_st_state_0, dir_bit_is_store, bus_state[0], bus_decode_flags_1.opcode_is_shift_xx);
next_nz_mux_common = Cpnt_4OR(next_nz_mux_main, next_nz_mux_main_extended, next_nz_mux_RAC, bus_decode_flags_2.load_weight);
next_n_mux_hold = ~Cpnt_2OR(next_nz_mux_common, next_xnzvc_mux_cplx_clr);//,bus_decode_flags_2.load_weight);
next_N_specific = Cpnt_4x2AND_OR(next_nz_mux_main,bus_rn_arith_flags.main_rn_input_mux_is_n, next_nz_mux_main_extended,bus_rn_arith_flags.main_rn_input_mux_is_n, next_nz_mux_RAC,bus_alu_flags.RA_mux_is_n, next_n_mux_hold, bus_PS[WiC_PS_FLAG_INDEX_N]);

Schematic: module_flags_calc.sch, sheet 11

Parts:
CMP65: 2AND
CMP66: 3OR
CMP67: 8X2AND_OR

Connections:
ADD2_IS_Z: CMP67.P$5 (C0); also elsewhere on the board
BIT_TEST_RESULT: CMP67.P$9 (E1); also elsewhere on the board
FLAG_Z: CMP67.P$7 (D0); also elsewhere on the board
LOAD_WEIGHT: CMP67.P$6 (C1); also elsewhere on the board
MAIN_RN_INPUT_MUX_IS_Z: CMP67.P$15 (H1); also elsewhere on the board
MAIN_RN_INPUT_MUX_IS_Z_EXTENDED: CMP67.P$14 (G2); also elsewhere on the board
unnamed: CMP67.P$1 (A0), CMP67.P$2 (A1), CMP67.P$3 (B0), CMP67.P$4 (B1)
NEXT_NZ_MUX_COMMON: CMP66.P$1 (0); also elsewhere on the board
NEXT_NZ_MUX_MAIN: CMP67.P$16 (H2); also elsewhere on the board
NEXT_NZ_MUX_RAC: CMP67.P$12 (F2); also elsewhere on the board
NEXT_XNZVC_MUX_CPLX_CLR: CMP66.P$2 (1); also elsewhere on the board
NEXT_Z_HOLD: CMP66.OUT_M (N), CMP67.P$8 (D1)
NEXT_Z_MUX_BIT_TEST: CMP65.OUT_P, CMP66.P$3 (2), CMP67.P$10 (E2)
NEXT_Z_SPECIFIC: CMP67.OUT_P; also elsewhere on the board
OPCODE_IS_BIT_XX: CMP65.P$1 (1); also elsewhere on the board
OPCODE_IS_X_ARITH: CMP67.P$13 (G1); also elsewhere on the board
RA_MUX_IS_Z: CMP67.P$11 (F1); also elsewhere on the board
STATE_3: CMP65.P$2 (2); also elsewhere on the board

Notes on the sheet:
next_z_mux_bit_test = Cpnt_2AND(bus_state[3], bus_decode_flags_2.opcode_is_bit_xx);
next_z_mux_hold = ~Cpnt_3OR(next_nz_mux_common, next_z_mux_bit_test, next_xnzvc_mux_cplx_clr);//,bus_decode_flags_2.load_weight);
next_Z_specific = Cpnt_8x2AND_OR(next_nz_mux_main,bus_rn_arith_flags.main_rn_input_mux_is_z, next_nz_mux_main_extended,main_rn_input_mux_is_z_extended, next_nz_mux_RAC,bus_alu_flags.RA_mux_is_z, next_z_mux_bit_test,bus_alu_flags.bit_test_result, next_z_mux_hold, bus_PS[WiC_PS_FLAG_INDEX_Z], bus_dec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

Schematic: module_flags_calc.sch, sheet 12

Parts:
CMP68, CMP69: 2X2AND_OR
CMP70: 2AND
CMP75: 1BUF

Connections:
FLAG_F0: CMP68.P$1 (A0); also elsewhere on the board
FLAG_F1: CMP69.P$1 (A0); also elsewhere on the board
HOLD_F0_F1: CMP68.P$2 (A1), CMP69.P$2 (A1), CMP75.N
H_COUNT_IS_15: CMP70.P$1 (1); also elsewhere on the board
LOAD_F0_F1: CMP68.P$4 (B1), CMP69.P$3 (B0), CMP75.P
NEXT_F0_SPECIFIC: CMP68.OUT_P; also elsewhere on the board
NEXT_F1_SPECIFIC: CMP69.OUT_P; also elsewhere on the board
NEXT_F3_SPECIFIC: CMP70.OUT_P; also elsewhere on the board
R0_IS_N: CMP68.P$3 (B0); also elsewhere on the board
R1_IS_N: CMP69.P$4 (B1); also elsewhere on the board
STATE_0: CMP75.IN; also elsewhere on the board
STATE_13: CMP70.P$2 (2); also elsewhere on the board

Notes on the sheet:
next_f0 = Cpnt_2x2AND_OR( bus_state[0], bus_rn_arith_flags.r0_is_n, ~bus_state[0], bus_PS[WiC_PS_FLAG_INDEX_F0]);
next_f1 = Cpnt_2x2AND_OR( bus_state[0], bus_rn_arith_flags.r1_is_n, ~bus_state[0], bus_PS[WiC_PS_FLAG_INDEX_F1]);
next_f2 = reset_signal;
next_f3 = Cpnt_2AND(bus_state[13],bus_decode_flags_2.h_count_is_15);

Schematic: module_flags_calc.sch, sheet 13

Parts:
CMP16: 1BUF
CMP17: 2X3AND_OR
CMP71, CMP73: 2OR
CMP72, CMP74: 2X2AND_OR

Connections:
DIV_BY_ZERO: CMP71.P$1 (A2), CMP72.P$3 (B0), CMP72.P$4 (B1); also elsewhere on the board
FLAG_F4: CMP72.P$1 (A0); also elsewhere on the board
FLAG_F5: CMP74.P$1 (A0); also elsewhere on the board
FLAG_F6: CMP17.P$1 (A0); also elsewhere on the board
HOLD_F6: CMP16.N, CMP17.P$2 (A1), CMP17.P$3 (A2)
H_3: CMP17.P$5 (B1); also elsewhere on the board
H_5: CMP17.P$4 (B0); also elsewhere on the board
LOAD_F6: CMP16.P, CMP17.P$6 (B2)
NEXT_F4_HOLD: CMP71.OUT_M (N), CMP72.P$2 (A1)
NEXT_F4_SPECIFIC: CMP72.OUT_P; also elsewhere on the board
NEXT_F5_HOLD: CMP73.OUT_M (N), CMP74.P$2 (A1)
NEXT_F5_SPECIFIC: CMP74.OUT_P; also elsewhere on the board
NEXT_F6_SPECIFIC: CMP17.OUT_P; also elsewhere on the board
STATE_1: CMP16.IN; also elsewhere on the board
TAKE_INTERRUPT: CMP73.P$2 (A1), CMP74.P$3 (B0), CMP74.P$4 (B1); also elsewhere on the board
TRAP_STATE_7: CMP71.P$2 (A1), CMP73.P$1 (A2); also elsewhere on the board

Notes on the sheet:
next_f4_mux_hold = ~Cpnt_2OR(bus_decode_flags_2.trap_state_7, bus_decode_flags_2.div_by_zero); next_f4 = Cpnt_2x2AND_OR(bus_decode_flags_2.div_by_zero, bus_decode_flags_2.div_by_zero, next_f4_mux_hold, bus_PS[WiC_PS_FLAG_INDEX_F4]);
next_f5_mux_hold = ~Cpnt_2OR(bus_decode_flags_2.trap_state_7, bus_decode_flags_2.take_interrupt); next_f5 = Cpnt_2x2AND_OR(bus_decode_flags_2.take_interrupt, bus_decode_flags_2.take_interrupt, next_f5_mux_hold, bus_PS[WiC_PS_FLAG_INDEX_F5]);
next_f6 = Cpnt_2x3AND_OR(~bus_state[1],~bus_state[1],bus_PS[WiC_PS_FLAG_INDEX_F6], bus_state[1],bus_H[5],bus_H[3]);

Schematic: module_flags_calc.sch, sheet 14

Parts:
CMP18: 2OR
CMP32, CMP33: 2X2AND_OR

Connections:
NEXT_XNZVC_MUX_LOGIC: CMP18.P$2 (A1), CMP32.OUT_P; also elsewhere on the board
NEXT_XNZVC_MUX_MEMORY: CMP18.P$1 (A2), CMP33.OUT_P; also elsewhere on the board
NEXT_XNZVC_MUX_SPECIFIC: CMP18.OUT_M (N); also elsewhere on the board
OPCODE_IS_ANDI_PS: CMP32.P$3 (B0); also elsewhere on the board
OPCODE_IS_ORI_PS: CMP32.P$1 (A0); also elsewhere on the board
OPCODE_IS_POP_PS: CMP33.P$4 (B1); also elsewhere on the board
STATE_3: CMP32.P$2 (A1), CMP32.P$4 (B1); also elsewhere on the board
STATE_5: CMP33.P$3 (B0); also elsewhere on the board
STATE_8: CMP33.P$1 (A0), CMP33.P$2 (A1); also elsewhere on the board

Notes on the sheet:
next_xnzvc_mux_logic = Cpnt_2x2AND_OR(bus_state[3], bus_decode_flags_1.opcode_is_andi_ps, bus_state[3], bus_decode_flags_1.opcode_is_ori_ps);
next_xnzvc_mux_memory = Cpnt_2x2AND_OR(bus_state[5], bus_decode_flags_1.opcode_is_pop_ps,// pop ps bus_state[8],bus_state[8]); //reti
next_xnzvc_flags_specific = ~Cpnt_2OR(next_xnzvc_mux_logic, next_xnzvc_mux_memory);

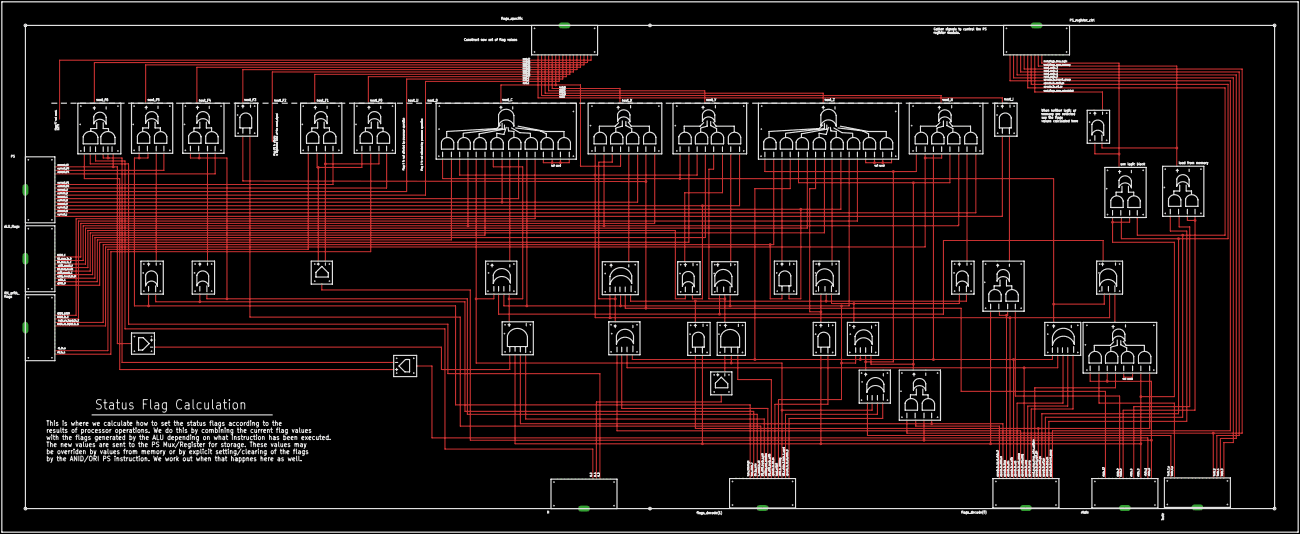
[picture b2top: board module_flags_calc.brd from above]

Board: 2 copper layers, 1397.0 x 571.5 mm, 50 parts (0 on the bottom side), 117 nets.
